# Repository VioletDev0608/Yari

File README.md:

# Yari
Yari is a 36-key column-staggered choc split keyboard. It is designed to reduce the required thumb movement beneath the palm.
It has 1 LED to indicate battery levels, splayed pinky and row columns, and is meant to be used with two Supermini nRF52840 microcontrollers. It features an EC11 rotary encoder and extra key on the left half that can be used to switch layers, etc.

## Features:
- 37 Keys
- Column staggered
- Choc v1
- Splayed pinky and row columns
- 1 LED for battery indication
- ZMK support
- Wireless
- EC11 Rotary Encoder

## CAD Model:

The case is a open style with no walls surrounding the switches and just a simple tray to mount the keyboard to and prevent dust from getting into the assembly.
The assembly itself is quite simple
Use a soldering iron to heat up the threaded screw inserts and help it melt its way into the slightly undersized standoff holes. Secure the PCB using the M2 screws. 

Added a version with a split case design with holes at the power button and a cutout at the MCU.

## PCB

PCB was made entirely in Kicad and rotated to minimize the costs when fabricating the PCB. 
There are some quotes on the palm so check it out!

## Firmware

Firmware is based on ZMK!
Hasn't been tested yet...

## BOM

Check [BOM.csv](https://github.com/VioletDev0608/Yari/blob/main/BOM/BOM%20-%20Yari.csv) for all parts needed to build this keyboard!
It comes out to about 98 dollars using aliexpress and JLCPCB to fabricate the PCB!

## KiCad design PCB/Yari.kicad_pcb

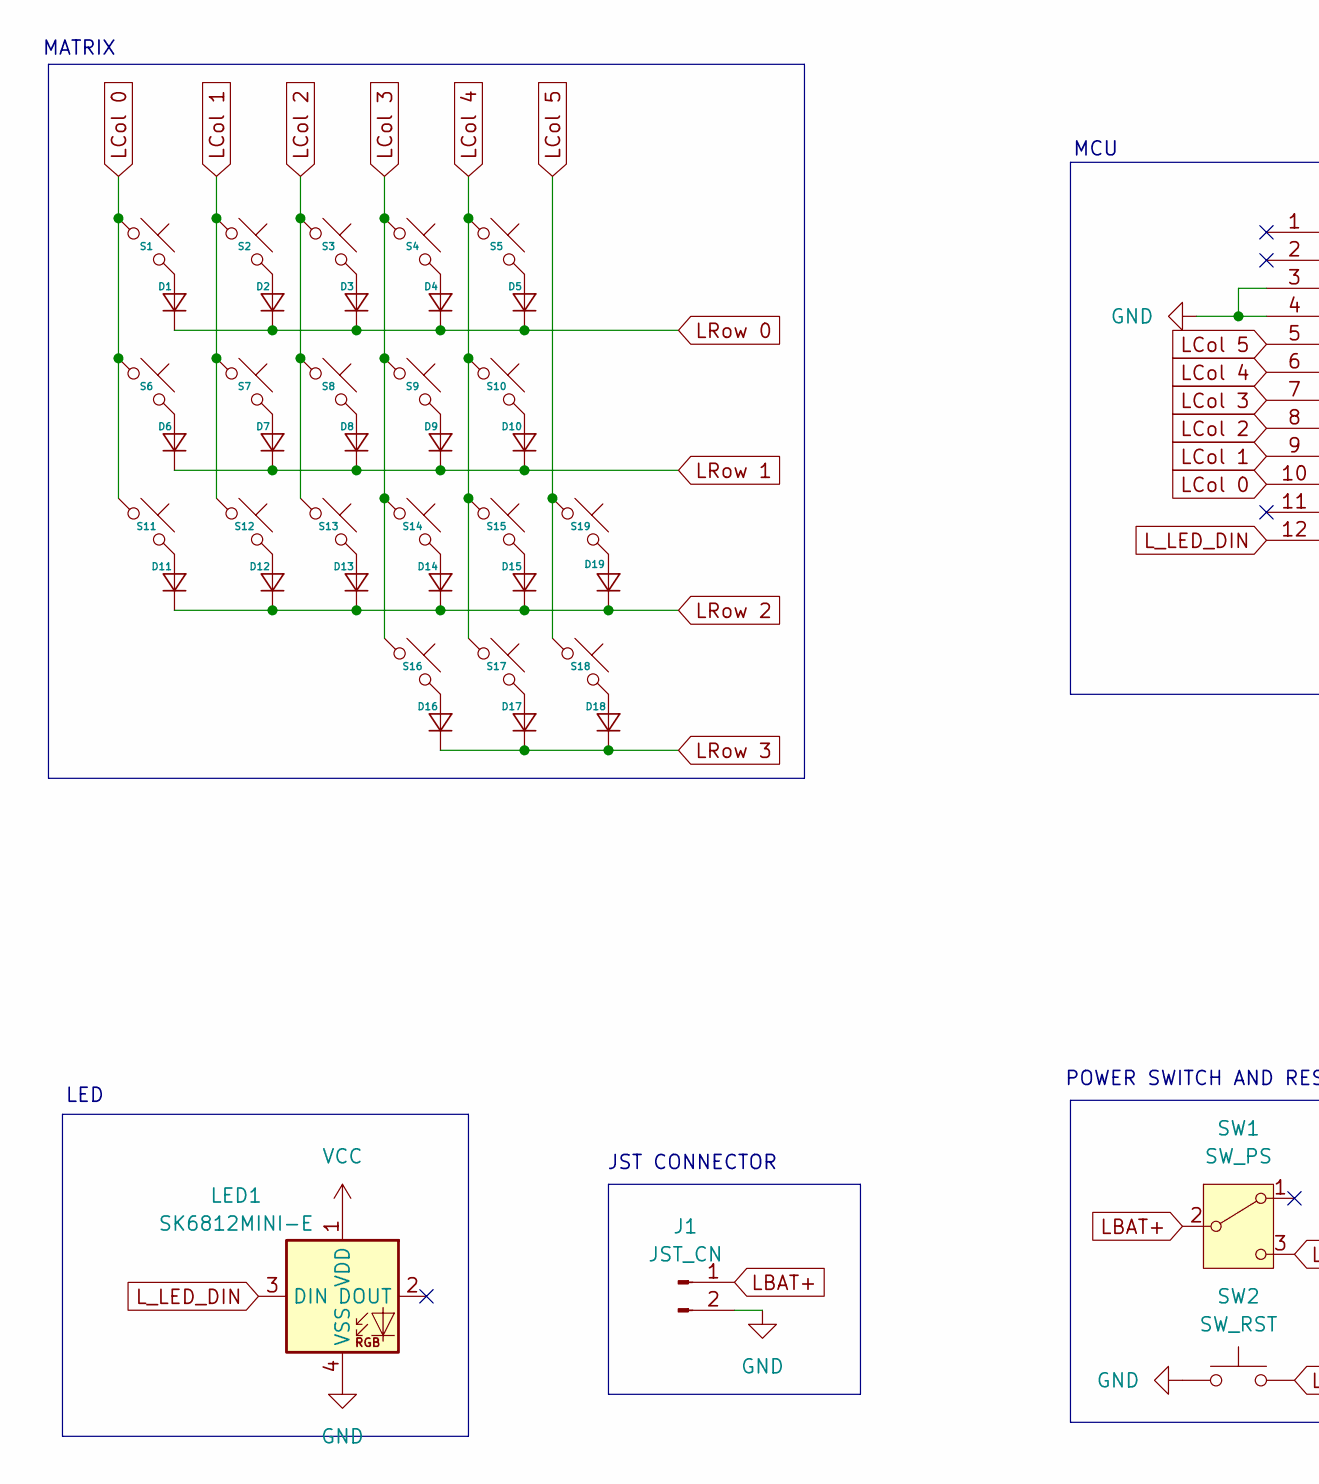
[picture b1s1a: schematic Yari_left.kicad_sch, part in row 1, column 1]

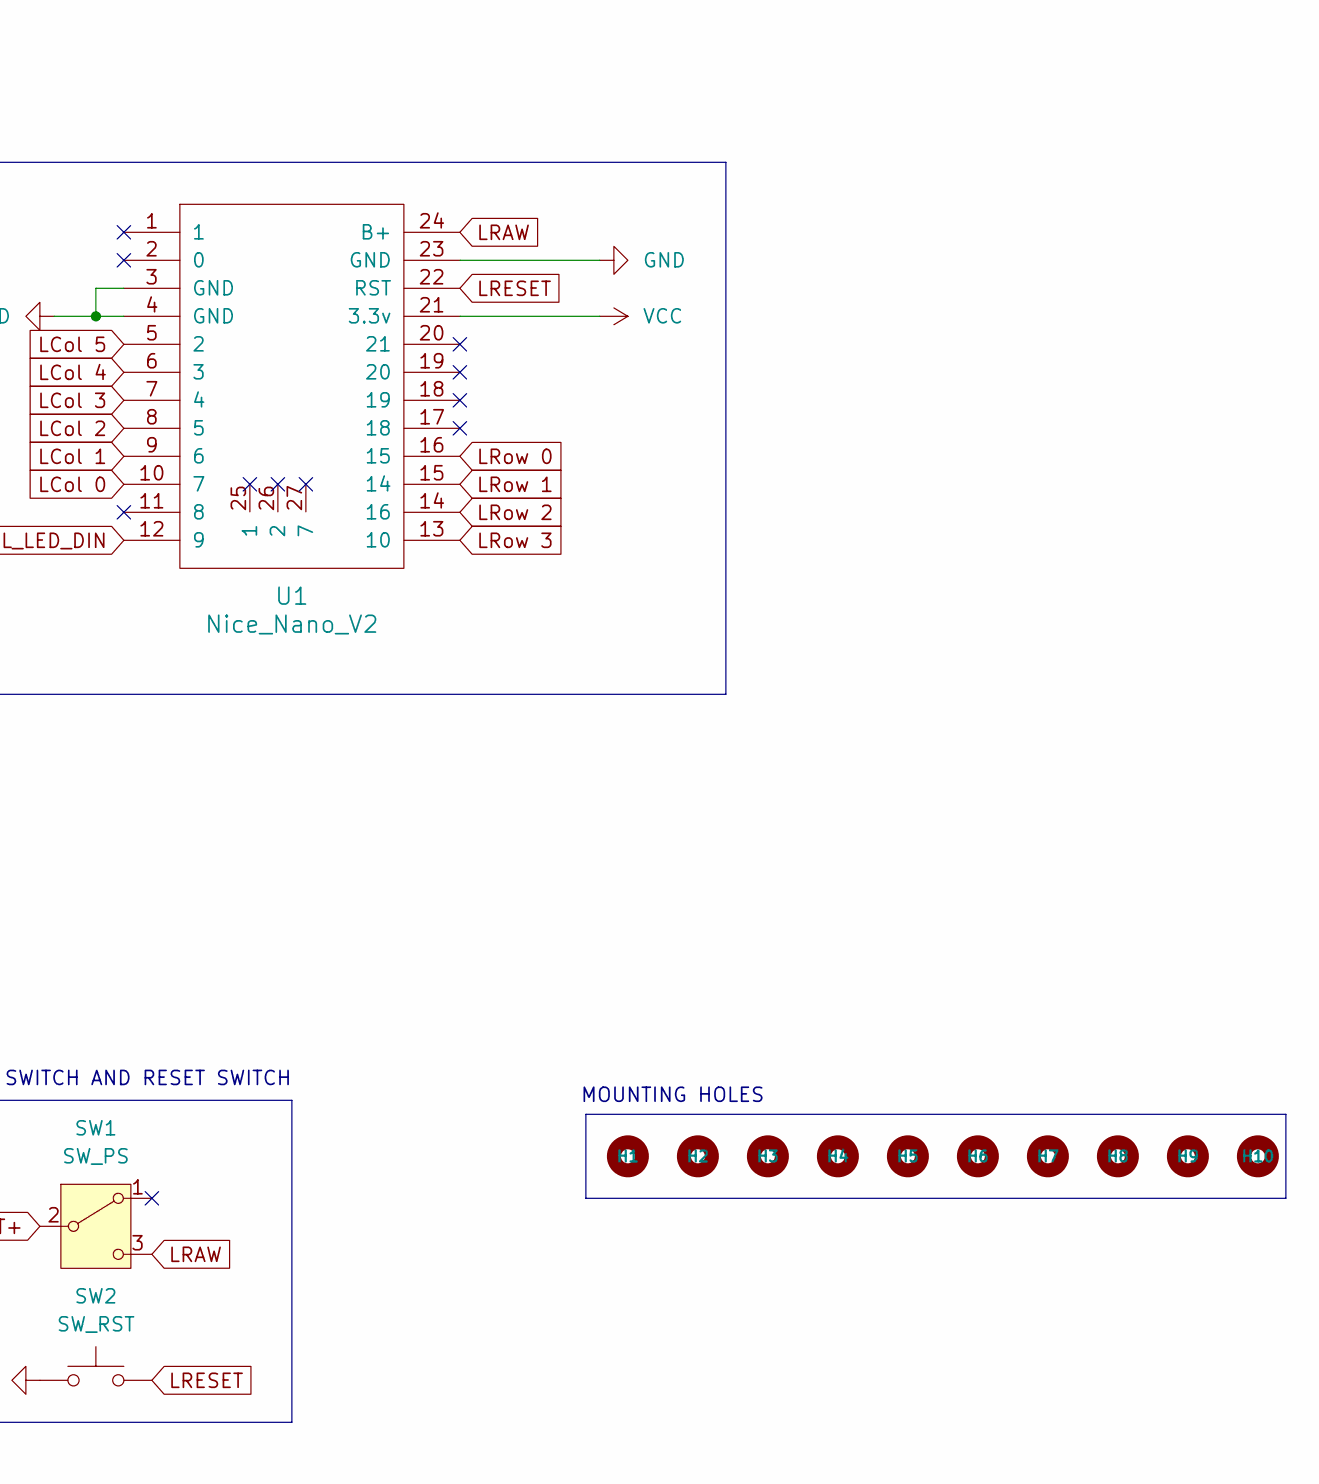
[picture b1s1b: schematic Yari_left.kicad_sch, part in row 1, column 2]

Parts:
D1, D2, D3, D4, D5, D6, D7, D8, D9, D10, D11, D12, D13, D14, D15, D16, D17, D18, D19: Diode_SOD-123
H1, H2, H3, H4, H5, H6, H7, H8, H9, H10: MountingHole_2.2mm_M2_DIN965
J1: JST_CN; JST_PH_S2B-PH-K_1x02_P2.00mm_Horizontal
LED1: SK6812MINI-E; LED_6028R
S1, S2, S3, S4, S5, S6, S7, S8, S9, S10, S11, S12, S13, S14, S15, S16, S17, S18, S19: Hotswap_Choc_V1_1.00u
SW1: SW_PS; SW_MSK12C02-HB
SW2: SW_RST; SW_SPST_B3U-1000P
U1: Nice_Nano_V2; Nice_Nano_V2_Flipped

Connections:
GND: J1.2, LED1.4 (VSS), SW2.1, U1.3 (GND), U1.4 (GND), U1.23 (GND); also elsewhere on the board
LBAT+: J1.1, SW1.2 (B)
LCol 0: S1.1, S6.1, S11.1, U1.10 (7)
LCol 1: S2.1, S7.1, S12.1, U1.9 (6)
LCol 2: S3.1, S8.1, S13.1, U1.8 (5)
LCol 3: S4.1, S9.1, S14.1, S16.1, U1.7 (4)
LCol 4: S5.1, S10.1, S15.1, S17.1, U1.6 (3)
LCol 5: S18.1, S19.1, U1.5 (2)
LRAW: SW1.3 (C), U1.24 (B+)
LRESET: SW2.2, U1.22 (RST)
LRow 0: D1.1 (K), D2.1 (K), D3.1 (K), D4.1 (K), D5.1 (K), U1.16 (15)
LRow 1: D6.1 (K), D7.1 (K), D8.1 (K), D9.1 (K), D10.1 (K), U1.15 (14)
LRow 2: D11.1 (K), D12.1 (K), D13.1 (K), D14.1 (K), D15.1 (K), D19.1 (K), U1.14 (16)
LRow 3: D16.1 (K), D17.1 (K), D18.1 (K), U1.13 (10)
L_LED_DIN: LED1.3 (DIN), U1.12 (9)
unnamed: D1.2 (A), S1.2
unnamed: D2.2 (A), S2.2
unnamed: D3.2 (A), S3.2
unnamed: D4.2 (A), S4.2
unnamed: D5.2 (A), S5.2
unnamed: D6.2 (A), S6.2
unnamed: D7.2 (A), S7.2
unnamed: D8.2 (A), S8.2
unnamed: D9.2 (A), S9.2
unnamed: D10.2 (A), S10.2
unnamed: D11.2 (A), S11.2
unnamed: D12.2 (A), S12.2
unnamed: D13.2 (A), S13.2
unnamed: D14.2 (A), S14.2
unnamed: D15.2 (A), S15.2
unnamed: D16.2 (A), S16.2
unnamed: D17.2 (A), S17.2
unnamed: D18.2 (A), S18.2
unnamed: D19.2 (A), S19.2
VCC: LED1.1 (VDD), U1.21 (3.3v); also elsewhere on the board

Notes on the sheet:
MATRIX
JST CONNECTOR
POWER SWITCH AND RESET SWITCH
MCU
MOUNTING HOLES
LED

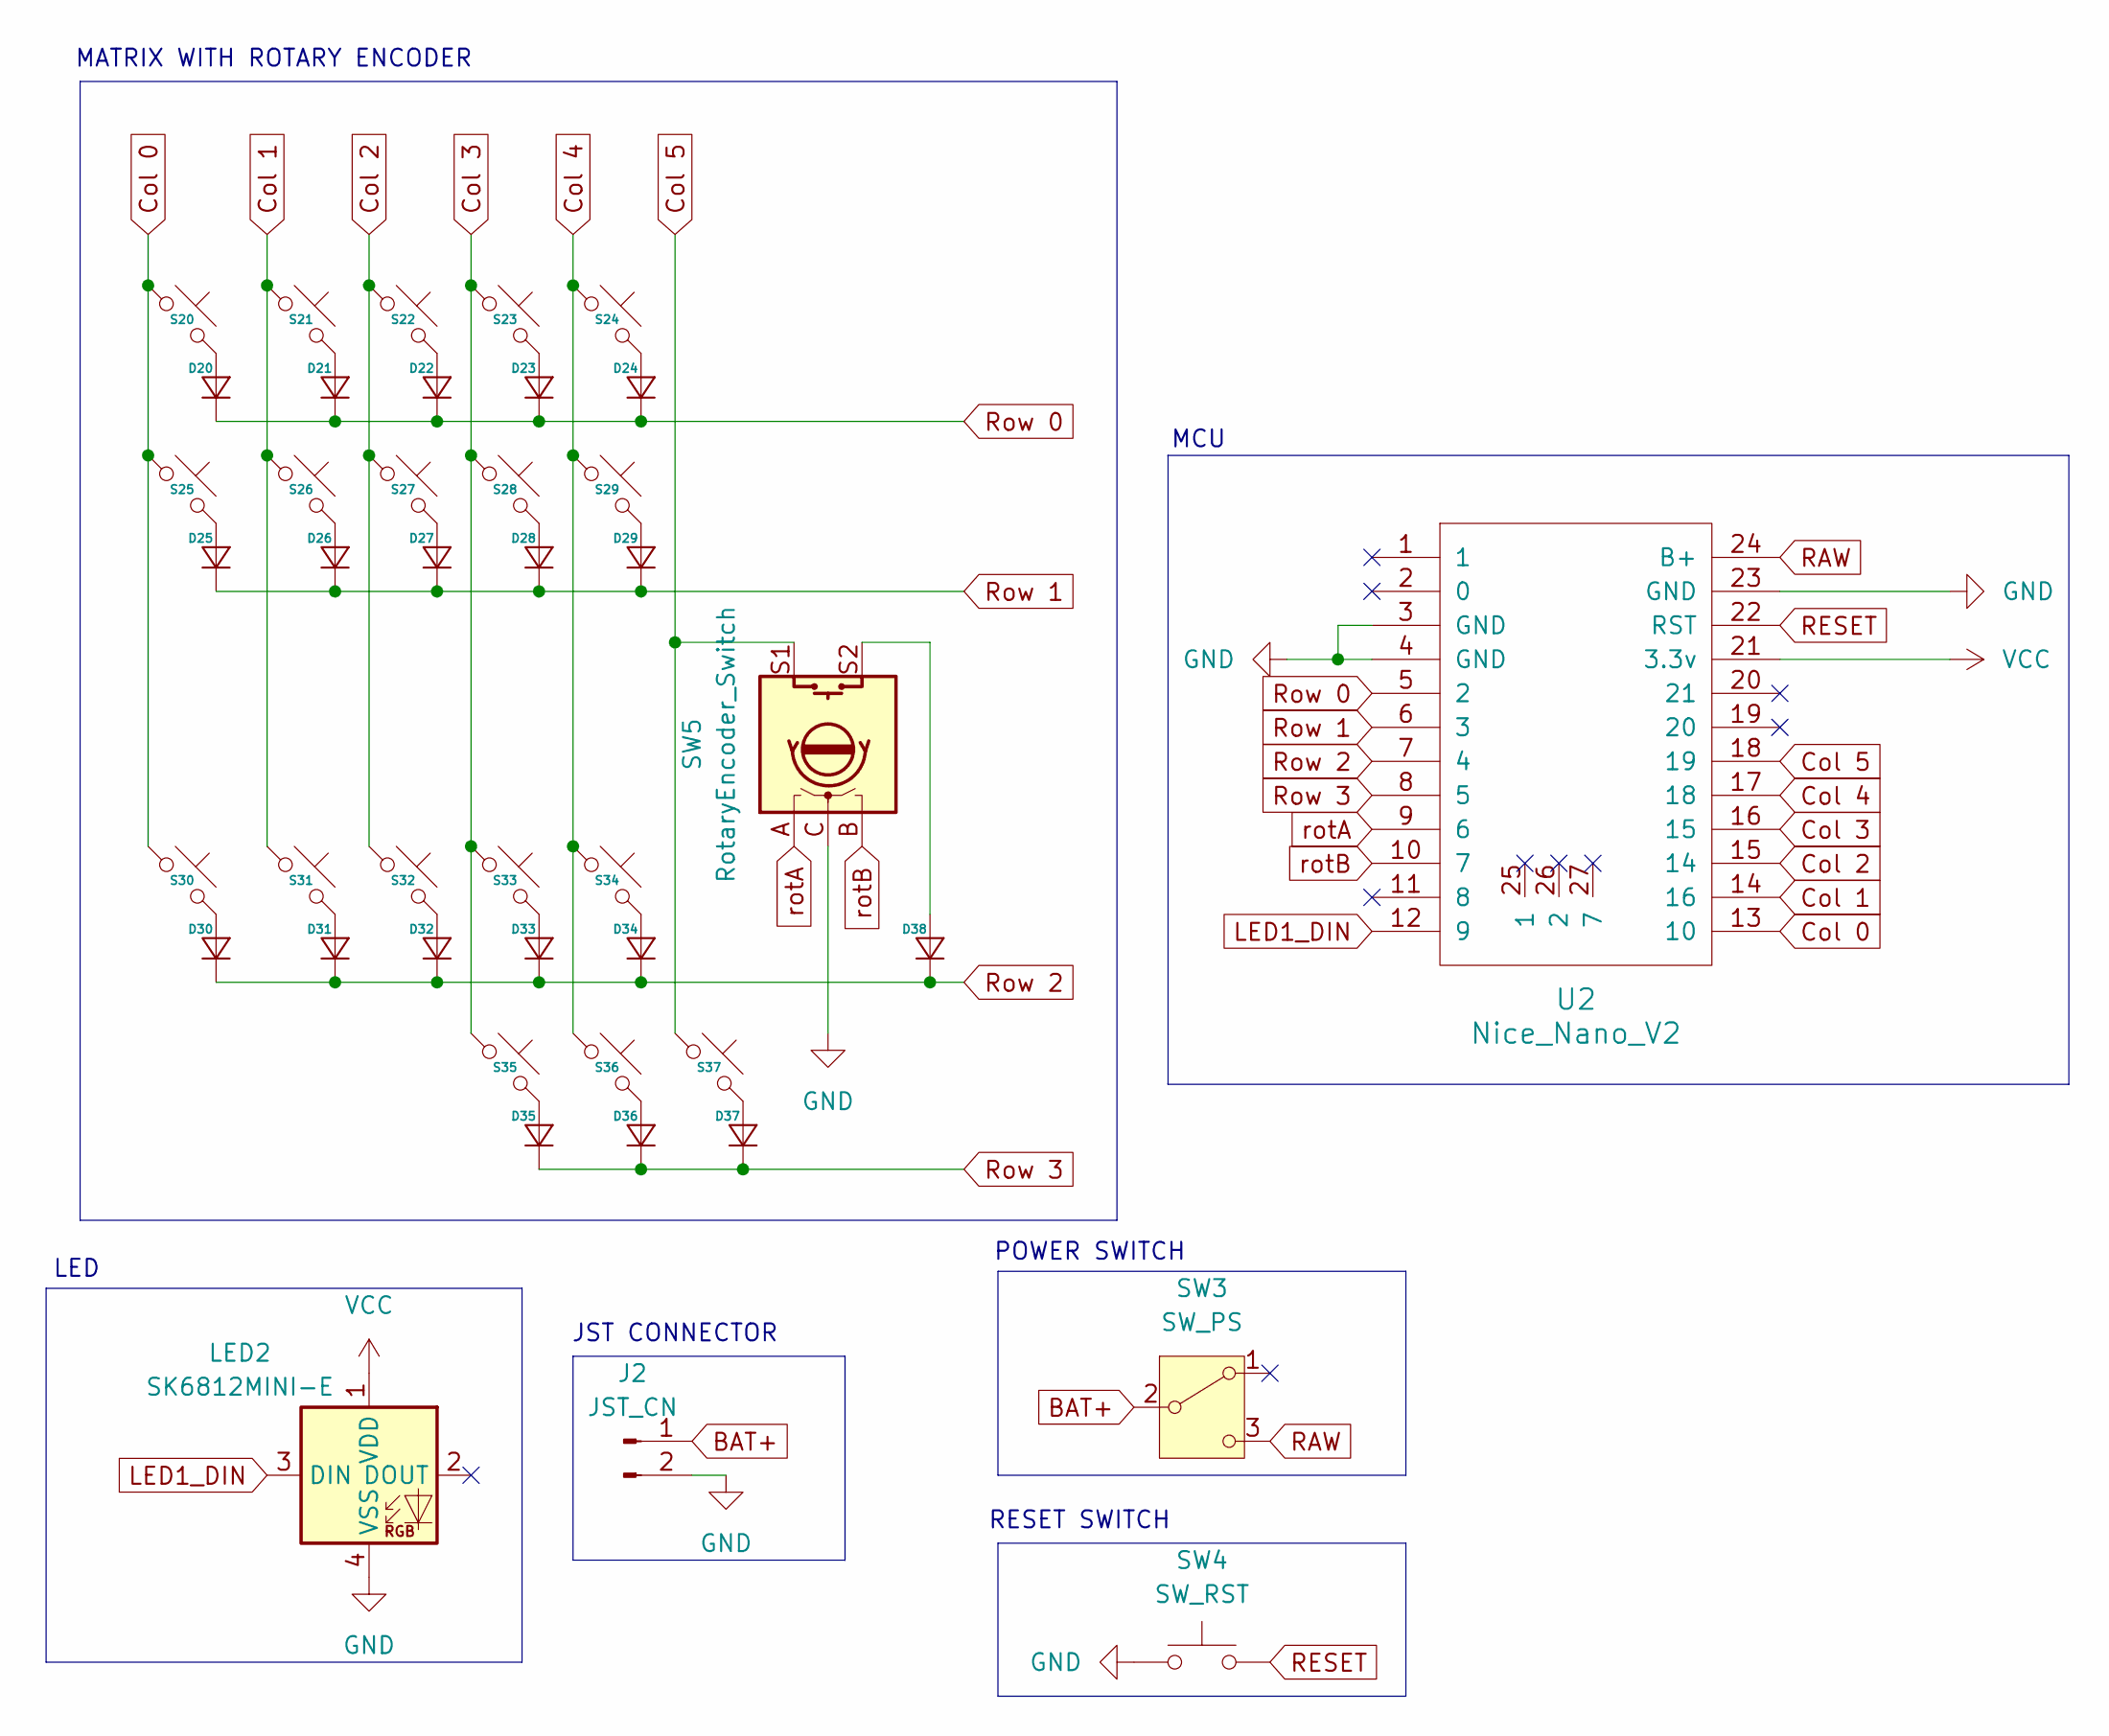
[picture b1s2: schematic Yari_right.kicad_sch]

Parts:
D20, D21, D22, D23, D24, D25, D26, D27, D28, D29, D30, D31, D32, D33, D34, D35, D36, D37, D38: Diode_SOD-123
J2: JST_CN; JST_PH_S2B-PH-K_1x02_P2.00mm_Horizontal
LED2: SK6812MINI-E; LED_6028R
S20, S21, S22, S23, S24, S25, S26, S27, S28, S29, S30, S31, S32, S33, S34, S35, S36, S37: Hotswap_Choc_V1_1.00u
SW3: SW_PS; SW_MSK12C02-HB
SW4: SW_RST; SW_SPST_B3U-1000P
SW5: RotaryEncoder_Switch; ROT_Alps_EC11E-Switch
U2: Nice_Nano_V2; Nice_Nano_V2_Flipped

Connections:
BAT+: J2.1, SW3.2 (B)
Col 0: S20.1, S25.1, S30.1, U2.13 (10)
Col 1: S21.1, S26.1, S31.1, U2.14 (16)
Col 2: S22.1, S27.1, S32.1, U2.15 (14)
Col 3: S23.1, S28.1, S33.1, S35.1, U2.16 (15)
Col 4: S24.1, S29.1, S34.1, S36.1, U2.17 (18)
Col 5: S37.1, SW5.S1, U2.18 (19)
GND: J2.2, LED2.4 (VSS), SW4.1, SW5.C, U2.3 (GND), U2.4 (GND), U2.23 (GND); also elsewhere on the board
LED1_DIN: LED2.3 (DIN), U2.12 (9)
unnamed: D20.2 (A), S20.2
unnamed: D21.2 (A), S21.2
unnamed: D22.2 (A), S22.2
unnamed: D23.2 (A), S23.2
unnamed: D24.2 (A), S24.2
unnamed: D25.2 (A), S25.2
unnamed: D26.2 (A), S26.2
unnamed: D27.2 (A), S27.2
unnamed: D28.2 (A), S28.2
unnamed: D29.2 (A), S29.2
unnamed: D30.2 (A), S30.2
unnamed: D31.2 (A), S31.2
unnamed: D32.2 (A), S32.2
unnamed: D33.2 (A), S33.2
unnamed: D34.2 (A), S34.2
unnamed: D35.2 (A), S35.2
unnamed: D36.2 (A), S36.2
unnamed: D37.2 (A), S37.2
unnamed: D38.2 (A), SW5.S2
RAW: SW3.3 (C), U2.24 (B+)
RESET: SW4.2, U2.22 (RST)
Row 0: D20.1 (K), D21.1 (K), D22.1 (K), D23.1 (K), D24.1 (K), U2.5 (2)
Row 1: D25.1 (K), D26.1 (K), D27.1 (K), D28.1 (K), D29.1 (K), U2.6 (3)
Row 2: D30.1 (K), D31.1 (K), D32.1 (K), D33.1 (K), D34.1 (K), D38.1 (K), U2.7 (4)
Row 3: D35.1 (K), D36.1 (K), D37.1 (K), U2.8 (5)
VCC: LED2.1 (VDD), U2.21 (3.3v); also elsewhere on the board
rotA: SW5.A, U2.9 (6)
rotB: SW5.B, U2.10 (7)

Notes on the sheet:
LED
MATRIX WITH ROTARY ENCODER
MCU
POWER SWITCH
RESET SWITCH
JST CONNECTOR

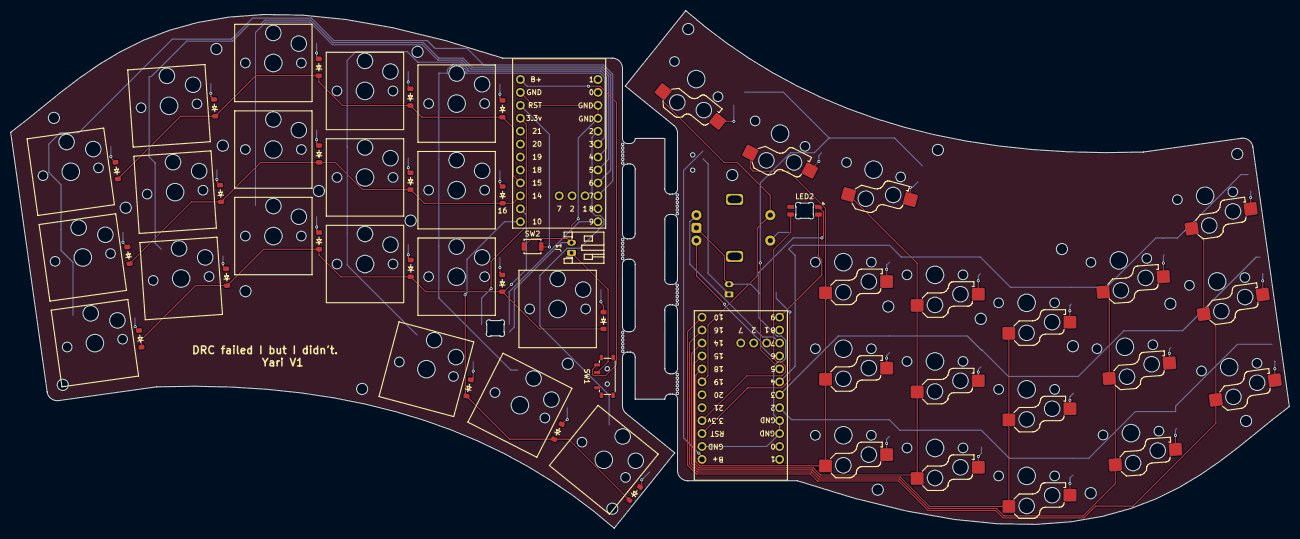
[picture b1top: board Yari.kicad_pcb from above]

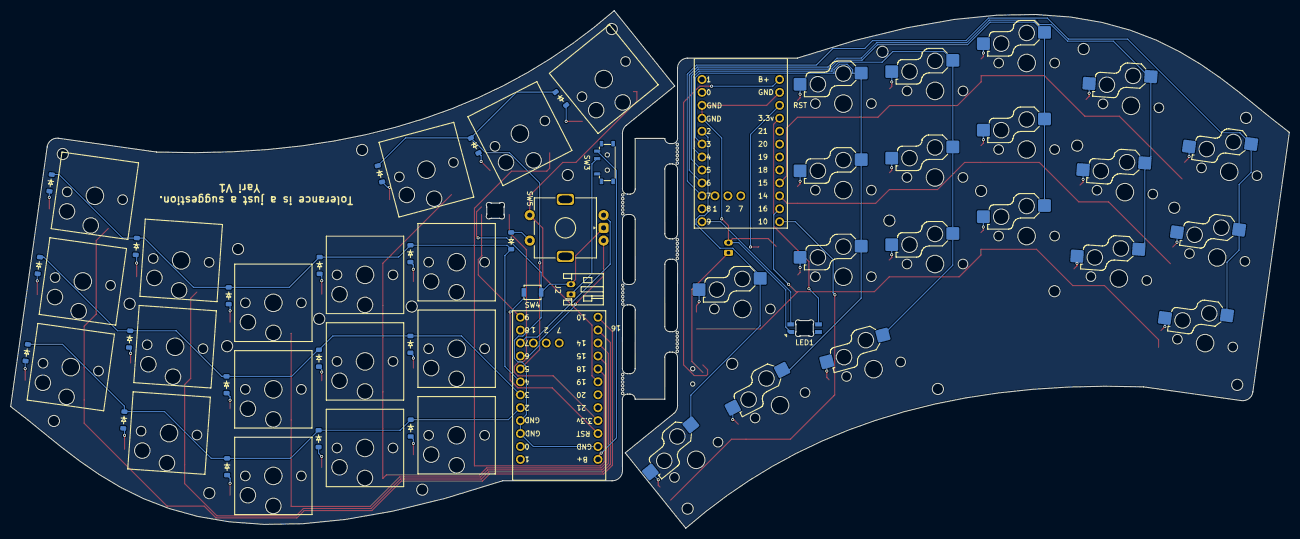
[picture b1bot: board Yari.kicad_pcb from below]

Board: 2 copper layers, 251.2 x 101.7 mm, 110 parts (45 on the bottom side), 70 nets.

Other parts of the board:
H1#2, H2#2, H3#2, H4#2, H5#2, H6#2, H6#3, H6#4, H6#5, H6#6, H7#2, H8#2, H9#2, H10#2: MountingHole_2.2mm_M2_DIN965

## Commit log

2025-12-16 Added images to README
    Added images and additional details to the CAD model, PCB, and firmware sections.
2025-12-16 Change license
2025-12-16 Add MIT License to the project
2026-01-14 Updated render images and added gerber files
2026-01-20 Updated Images for CAD models
2026-01-20 Correct key count from 38 to 36 in README
2026-01-20 Added BOM.csv and converted STL files to STEP
2026-02-17 Started over in Kicad
2026-02-17 Revise Yari keyboard specifications and BOM details
    Updated specifications for the Yari keyboard, including changes to the number of keys, LEDs, and PCB details. Added images and a link to the BOM for building the keyboard.
2026-02-19 Top Case STL and images
2026-02-19 Rename スクリーンショット 2026-02-19 234503.png to image16.png
2026-02-19 Add case version with proper walls and button holes
    Added a new version of the case with proper walls and holes for the MCU and power buttons.
2026-02-20 Top Case Update and BOM links
2026-02-20 Update case description and image for split design
2026-02-22 Fixed the hole in Right Top Case Bottom
